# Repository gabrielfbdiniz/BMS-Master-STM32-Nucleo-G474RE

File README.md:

# BMS Master — STM32 Nucleo G474RE (Formula ITA)
### ECU Central de Gerenciamento do Acumulador de Tração (20s18p)

Repositório oficial e unificado (**Monorepo**) de **Hardware**, **Firmware** e **Documentação de Engenharia** do BMS Master desenvolvido para o protótipo Formula SAE Electric da equipe **Formula ITA** (Temporada 2025-2026).

---

## Renderização 3D da Carrier Board

A placa **BMS Master Carrier Shield** é uma PCB de 4 camadas projetada para acoplar o núcleo de processamento **ST NUCLEO-G474RE** via conectores Morpho, integrando circuitos de proteção automotiva, barreira galvânica e interface com o circuito de segurança (SDC).

<div align="center">
  
  <p><em>Vista Isométrica Superior — Destaque para o transformador de pulso Pulse HMU2103NL (Iso-SPI), relé automotivo TE do SDC, regulador buck automotivo e conectores Molex Micro-Fit.</em></p>
</div>

<br>

### Galeria de Vistas 3D (KiCad 10 Raytracing)

| Perspectiva Superior (Iso Top) | Perspectiva Inferior (Iso Bottom) |
| :---: | :---: |
|  |  |
| **Vista Ortográfica Superior (Top View)** | **Vista Ortográfica Inferior (Bottom View)** |
|  |  |

---

## Destaques do Projeto de Hardware

* **Topologia do Acumulador:** 20 blocos em série, cada bloco com 18 células em paralelo (**20s18p = 360 células** formato 21700).
* **Processamento Central:** ST NUCLEO-G474RE (MCU ARM Cortex-M4F com FPU a 170 MHz, 512 kB Flash, 128 kB SRAM).
* **Barreira de Isolação Iso-SPI (FSAE EV4.8):** Transceptor ST `L99BM1TR` acoplado a transformador de isolação `Pulse HMU2103NL` ($\ge 2500\text{ V}_{RMS}$, creepage $\ge 4{,}0\text{ mm}$).
* **Interface SDC Hardware Latch:** Circuito biestável puramente em hardware com reset supervisionado, garantindo abertura mandatória da linha de shutdown em qualquer falha crítica.
* **Alimentação e Proteção GLV:** Buck automotivo `TI LMR36510` (12V $\to$ 5V) com supressor TVS SMAJ, diodo Schottky contra inversão de polaridade e filtragem para normas ISO 7637-2.
* **Comunicação Veicular:** CAN-FD isolada galvanicamente via transceptor `TI ISO1042` (suporte a até 5 Mbps).

---

## Estrutura do Repositório (Monorepo)

```text
BMS Master - STM - V0/
├── .gitignore                         # Regras de exclusão Git (KiCad, builds, temporários)
├── README.md                          # Visão geral, especificações e documentação rápida
├── docs/                              # Engenharia de sistemas, especificações e manuais
│   ├── schematics/                    # Esquemáticos oficiais em PDF vetorial
│   │   └── BMS_Master_Schematic.pdf   # Esquemático hierárquico vetorial completo (KiCad 10)
│   ├── PLANO_MESTRE_BMS_MASTER_CONSOLIDADO.md  # Especificação técnica completa do sistema
│   ├── MANUAL_OPERACIONAL_E_MONTAGEM_BMS.md    # Procedimentos de montagem, testes e comissionamento
│   ├── PLANO_DETECCAO_FUSIVEL_METODO_1.md      # Formulação matemática do algoritmo RLS e Z-score
│   ├── GUIA_ENSAIO_CARACTERIZACAO_CELULAS_21700.md # Manual de bancada HPPC (FreedomCAR)
│   └── ARQUITETURA_E_PLANEJAMENTO_BMS_MASTER.md    # Arquitetura conceitual e interfaces
│
├── hardware/                          # Projeto Eletrônico no KiCad 10
│   └── carrier_shield/                # Carrier Board de 4 camadas para NUCLEO-G474RE
│       ├── bms_carrier_shield.kicad_pro  # Projeto mestre KiCad
│       ├── bms_carrier_shield.kicad_sch  # Esquemático mestre
│       ├── bms_carrier_shield.kicad_pcb  # Layout de 4 camadas (Top/GND/PWR/Bot)
│       ├── 01_power_supply.kicad_sch     # Folha: Regulador GLV 12V -> 5V
│       ├── 02_isospi_barrier.kicad_sch   # Folha: Barreira Iso-SPI L99BM1TR + HMU2103NL
│       ├── 03_sdc_latch.kicad_sch        # Folha: Circuito Latch biestável do SDC
│       ├── 05_canfd_interface.kicad_sch  # Folha: Interface CAN-FD isolada ISO1042
│       ├── 06_nucleo_headers.kicad_sch   # Folha: Conectores Morpho NUCLEO-G474RE
│       ├── fp-lib-table, sym-lib-table   # Mapeamento local de bibliotecas
│       ├── libraries/                    # Modelos 3D (.stp/.wrl), símbolos e footprints
│       └── fabrication/                  # Pacote de manufatura e montagem SMT
│           ├── FABRICATION_NOTES.md      # Especificações para fabricação da placa
│           ├── gerbers/                  # Arquivos Gerber RS-274X e Drill Excellon (ZIP)
│           ├── bom/                      # Listas de materiais (CSV, TSV, Mouser, Interactive BOM)
│           └── cpl/                      # Arquivo de posicionamento Pick & Place (pos.csv)
│
├── renders/                           # Renderizações fotorrealistas em alta resolução da PCB (KiCad 10)
│   ├── master_render_iso_top.png
│   ├── master_render_iso_bottom.png
│   ├── master_render_top.png
│   └── master_render_bottom.png
│
├── firmware/                          # Código em C99 Puro (ARM Cortex-M4F & Simulação SIL)
│   ├── core/                          # Algoritmos puros desacoplados de hardware
│   │   ├── bms_types.h                # Definições da topologia 20s18p, limites e telemetria
│   │   ├── alg_fuse_detect.c/.h       # RLS incremental, Z-score e Pre-Flight Check de fusíveis
│   │   ├── alg_soc.c/.h               # Coulomb counting, tabela OCV e limites CCL/DCL dinâmicos
│   │   └── fsm_master.c/.h            # Máquina de estados finitos (FSAE EV4.8 / EV8)
│   ├── mock/                          # Motor de sensoriamento sintético de alta fidelidade
│   ├── tests_sil/                     # Testes de Software-in-the-Loop (SIL) no Host (PC)
│   └── tools/                         # Scripts de simulação e plotagem em Python
│
├── can/                               # Matriz de comunicação veicular CAN-FD
│   ├── README.md                      # Documentação das mensagens CAN e taxas de atualização
│   └── bms_can_matrix.dbc             # Arquivo DBC padronizado
│
└── simulation/                        # Simulação de circuitos analógicos (Proteus VSM)
    └── proteus_sdc_precharge/         # Circuito biestável SDC e transitório RC de pré-carga
```

---

## Software-in-the-Loop (SIL) & Validação de Algoritmos

O firmware foi projetado segundo a arquitetura de **Core Desacoplado**, permitindo que 100% dos algoritmos de segurança, estimativa de estado e detecção de anomalias sejam validados no computador host antes do deployment no microcontrolador:

1. **Detecção de Fusível Rompido via RLS:** Estima recursivamente a resistência interna $\hat{R}_i$ de cada bloco em tempo real durante a descarga ($0{,}833\text{ m}\Omega \to 0{,}882\text{ m}\Omega$, delta de $+49\ \mu\Omega$).
2. **Estimador de SOC Híbrido:** Integração Coulomb Counting compensada por OCV relaxado com limites dinâmicos de corrente de carga (CCL) e descarga (DCL).
3. **FSM Conforme FSAE:** Transições estritas entre `BOOT`, `PRECHARGE`, `DRIVE`, `CHARGING`, `FAULT` e travamento por Latch em caso de violação de envelope seguro.

<div align="center">
  
  <p><em>Curvas de resposta dinâmica: Corrente do perfil de corrida, tensões das células, evolução da resistência estimada por RLS com injeção de falha aos 20s e transições de estado da FSM.</em></p>
</div>

### Executando a Simulação SIL Localmente

No terminal, dentro do diretório `firmware/`:

```powershell
# 1. Compilar e rodar a simulação SIL nativa em C (60 segundos virtuais a 100 Hz)
clang -O2 -Wall -Icore -Imock tests_sil/main_sil_runner.c core/alg_fuse_detect.c core/alg_soc.c core/fsm_master.c mock/bms_mock_battery.c mock/drive_cycle.c -o tests_sil/sil_runner.exe -lm
.\tests_sil\sil_runner.exe

# 2. Gerar/atualizar os gráficos de telemetria
python tools/plot_telemetry.py
```

---

## Como Abrir o Projeto Eletrônico no KiCad 10

1. Abra o **KiCad 10**.
2. Selecione **Abrir Projeto** e aponte para:  
   `hardware/carrier_shield/bms_carrier_shield.kicad_pro`.
3. Para visualizar a placa em 3D:
   - Abra o editor de PCB (`bms_carrier_shield.kicad_pcb`).
   - Pressione <kbd>Alt</kbd> + <kbd>3</kbd> para abrir o **Visualizador 3D**.
   - As bibliotecas de modelos (`libraries/3dmodels/`) já estão configuradas relativamente no projeto.
4. Para consultar o esquemático em PDF sem abrir o KiCad:
   - Abra diretamente: [`docs/schematics/BMS_Master_Schematic.pdf`](docs/schematics/BMS_Master_Schematic.pdf).

---

## Documentação Técnica de Referência

Consulte a pasta [`docs/`](docs/) para aprofundamento técnico:
* [**Esquemático Oficial (PDF)**](docs/schematics/BMS_Master_Schematic.pdf) — Desenho esquemático elétrico completo vetorial.
* [**Plano Mestre Consolidado**](docs/PLANO_MESTRE_BMS_MASTER_CONSOLIDADO.md) — Documento mestre de especificação técnica e funcional.
* [**Manual Operacional e de Montagem**](docs/MANUAL_OPERACIONAL_E_MONTAGEM_BMS.md) — Roteiro detalhado de fabricação, montagem de chicotes e testes de bancada.
* [**Plano de Detecção de Fusível Rompido**](docs/PLANO_DETECCAO_FUSIVEL_METODO_1.md) — Formulação matemática do RLS incremental e teste Z-score.
* [**Guia de Caracterização de Células 21700**](docs/GUIA_ENSAIO_CARACTERIZACAO_CELULAS_21700.md) — Protocolo de ensaio experimental HPPC em bancada.

---

<div align="center">
  <sub>Formula ITA — Equipe de Formula SAE Elétrico do Instituto Tecnológico de Aeronáutica (ITA).</sub>
</div>

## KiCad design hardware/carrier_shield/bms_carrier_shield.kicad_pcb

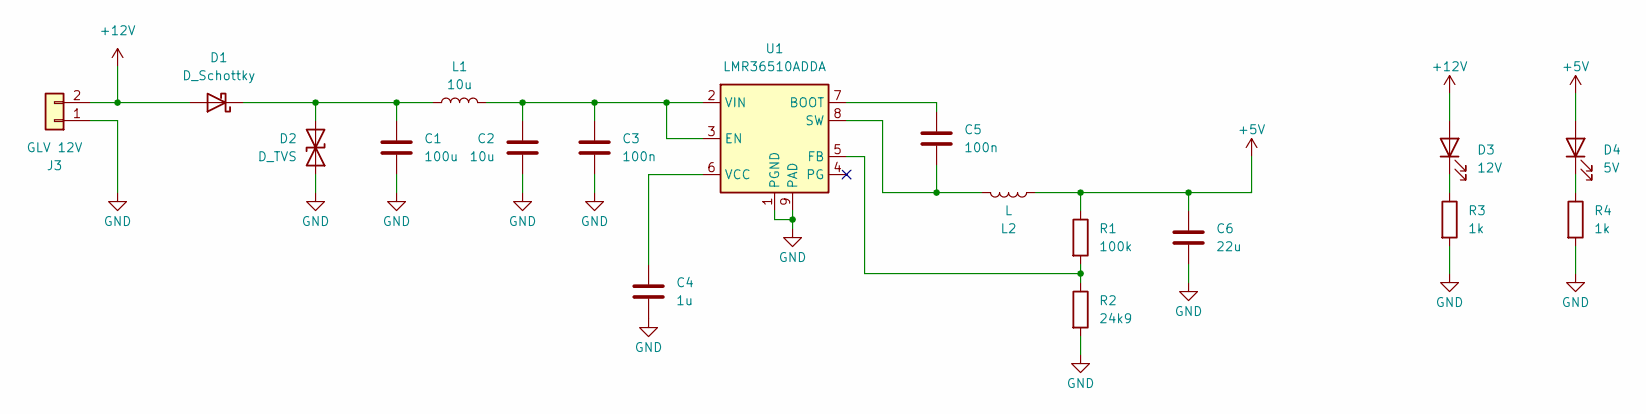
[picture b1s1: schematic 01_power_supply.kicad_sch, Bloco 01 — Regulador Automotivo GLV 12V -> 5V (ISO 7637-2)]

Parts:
C1: 100u; CP_Elec_8x10
C2: 10u; C_0805_2012Metric_Pad1.18x1.45mm_HandSolder
C3, C5: 100n; C_0603_1608Metric_Pad1.08x0.95mm_HandSolder
C4: 1u; C_0603_1608Metric_Pad1.08x0.95mm_HandSolder
C6: 22u; C_0805_2012Metric_Pad1.18x1.45mm_HandSolder
D1: D_Schottky; D_SMA
D2: D_TVS; D_SMA
D3: 12V; LED_0805_2012Metric_Pad1.15x1.40mm_HandSolder
D4: 5V; LED_0805_2012Metric_Pad1.15x1.40mm_HandSolder
J3: GLV 12V; AMASS_XT30U-F_1x02_P5.0mm_Vertical
L1: 10u; L_Bourns_SRR1260
L2: L; L_Bourns_SRR1260
R1: 100k; R_0603_1608Metric_Pad0.98x0.95mm_HandSolder
R2: 24k9; R_0603_1608Metric_Pad0.98x0.95mm_HandSolder
R3, R4: 1k; R_0603_1608Metric_Pad0.98x0.95mm_HandSolder
U1: LMR36510ADDA; Texas_HTSOP-8-1EP_3.9x4.9mm_P1.27mm_EP2.95x4.9mm_Mask2.4x3.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

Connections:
+5V: C6.1, D4.2 (A), L2.2, R1.1; also elsewhere on the board
+12V: D1.2 (A), D3.2 (A), J3.2; also elsewhere on the board
GND: C1.2, C2.2, C3.2, C4.2, C6.2, D2.1 (A1), J3.1, R2.2, R3.2, R4.2, U1.1 (PGND), U1.9 (PAD); also elsewhere on the board
unnamed: C1.1, D1.1 (K), D2.2 (A2), L1.1
unnamed: D3.1 (K), R3.1
unnamed: D4.1 (K), R4.1
unnamed: C5.1, U1.7 (BOOT)
unnamed: C2.1, C3.1, L1.2, U1.2 (VIN), U1.3 (EN)
unnamed: R1.2, R2.1, U1.5 (FB)
unnamed: C5.2, L2.1, U1.8 (SW)
unnamed: C4.1, U1.6 (VCC)

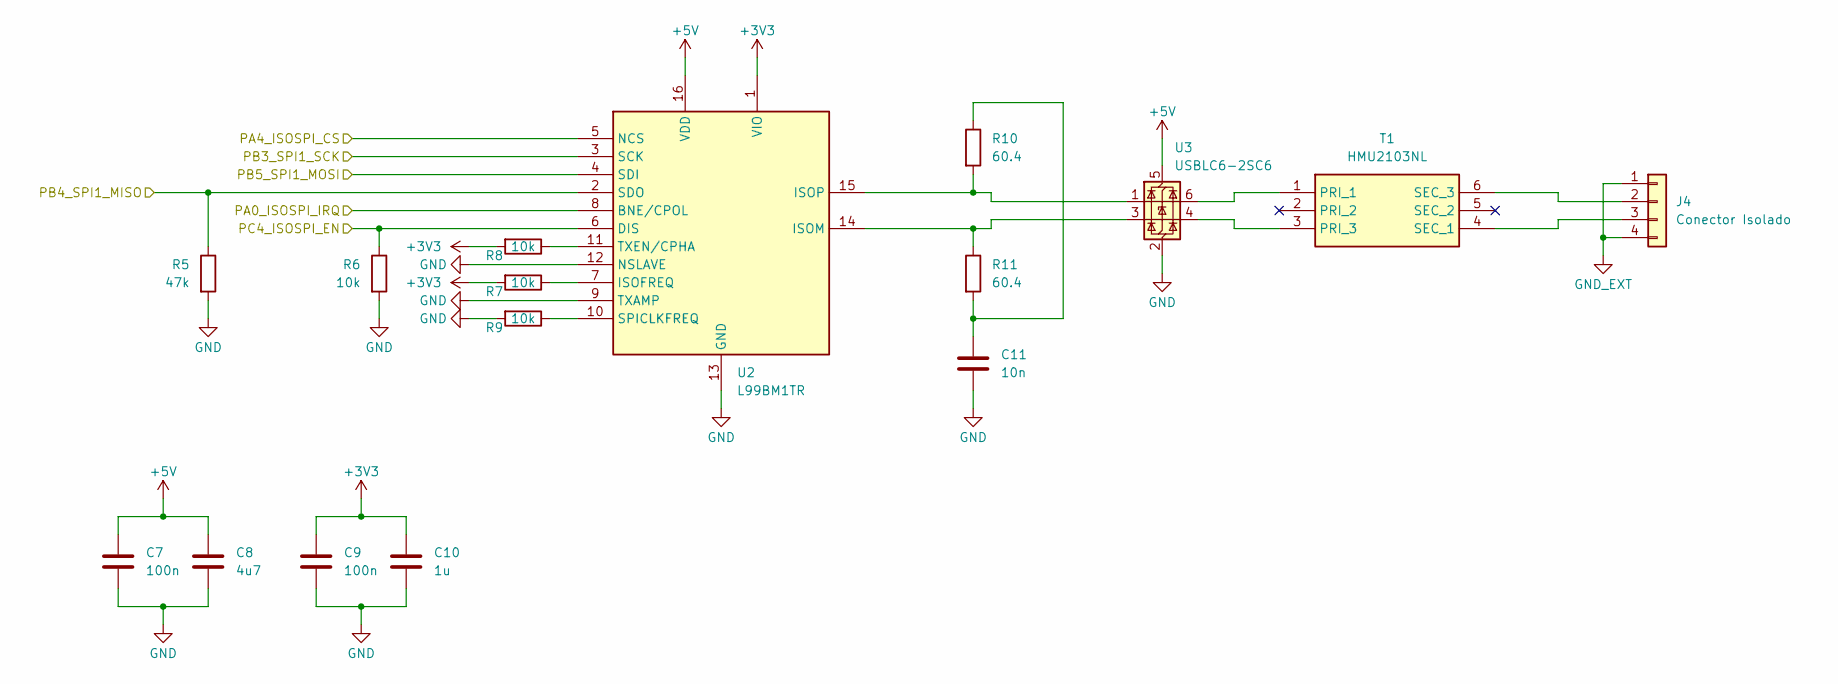
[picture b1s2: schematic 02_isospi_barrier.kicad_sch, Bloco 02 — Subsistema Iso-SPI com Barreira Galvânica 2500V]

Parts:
C7, C9: 100n; C_0603_1608Metric_Pad1.08x0.95mm_HandSolder
C8: 4u7; C_0805_2012Metric_Pad1.18x1.45mm_HandSolder
C10: 1u; C_0603_1608Metric_Pad1.08x0.95mm_HandSolder
C11: 10n; C_0603_1608Metric_Pad1.08x0.95mm_HandSolder
J4: Conector Isolado; Molex_Micro-Fit_3.0_43650-0400_1x04_P3.00mm_Horizontal
R5: 47k; R_0603_1608Metric_Pad0.98x0.95mm_HandSolder
R6, R7, R8, R9: 10k; R_0603_1608Metric_Pad0.98x0.95mm_HandSolder
R10, R11: 60.4; R_0603_1608Metric_Pad0.98x0.95mm_HandSolder
T1: HMU2103NL; Mouser Part Number 673-HMU2103NL
U2: L99BM1TR; SOIC-16_3.9x9.9mm_P1.27mm; Manufacturer_Part_Number L99BM1TR
U3: USBLC6-2SC6; SOT-23-6

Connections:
+3V3: C9.1, C10.1, R7.2, R8.2, U2.1 (VIO); also elsewhere on the board
+5V: C7.1, C8.1, U2.16 (VDD), U3.5 (VBUS); also elsewhere on the board
/05_Nucleo_G474RE_Morpho_Headers/PA0_ISOSPI_IRQ: U2.8 (BNE/CPOL); also elsewhere on the board
/05_Nucleo_G474RE_Morpho_Headers/PA4_ISOSPI_CS: U2.5 (NCS); also elsewhere on the board
/05_Nucleo_G474RE_Morpho_Headers/PB3_SPI1_SCK: U2.3 (SCK); also elsewhere on the board
/05_Nucleo_G474RE_Morpho_Headers/PB4_SPI1_MISO: R5.1, U2.2 (SDO); also elsewhere on the board
/05_Nucleo_G474RE_Morpho_Headers/PB5_SPI1_MOSI: U2.4 (SDI); also elsewhere on the board
/05_Nucleo_G474RE_Morpho_Headers/PC4_ISOSPI_EN: R6.1, U2.6 (DIS); also elsewhere on the board
GND: C7.2, C8.2, C9.2, C10.2, C11.2, R5.2, R6.2, R9.2, U2.9 (TXAMP), U2.12 (NSLAVE), U2.13 (GND), U3.2 (GND); also elsewhere on the board
GND_EXT: J4.1, J4.4
unnamed: C11.1, R10.1, R11.2
unnamed: J4.2, T1.6 (SEC_3)
unnamed: J4.3, T1.4 (SEC_1)
unnamed: T1.1 (PRI_1), U3.6 (I/O1)
unnamed: T1.3 (PRI_3), U3.4 (I/O2)
unnamed: R7.1, U2.7 (ISOFREQ)
unnamed: R11.1, U2.14 (ISOM), U3.3 (I/O2)
unnamed: R10.2, U2.15 (ISOP), U3.1 (I/O1)
unnamed: R9.1, U2.10 (SPICLKFREQ)
unnamed: R8.1, U2.11 (TXEN/CPHA)

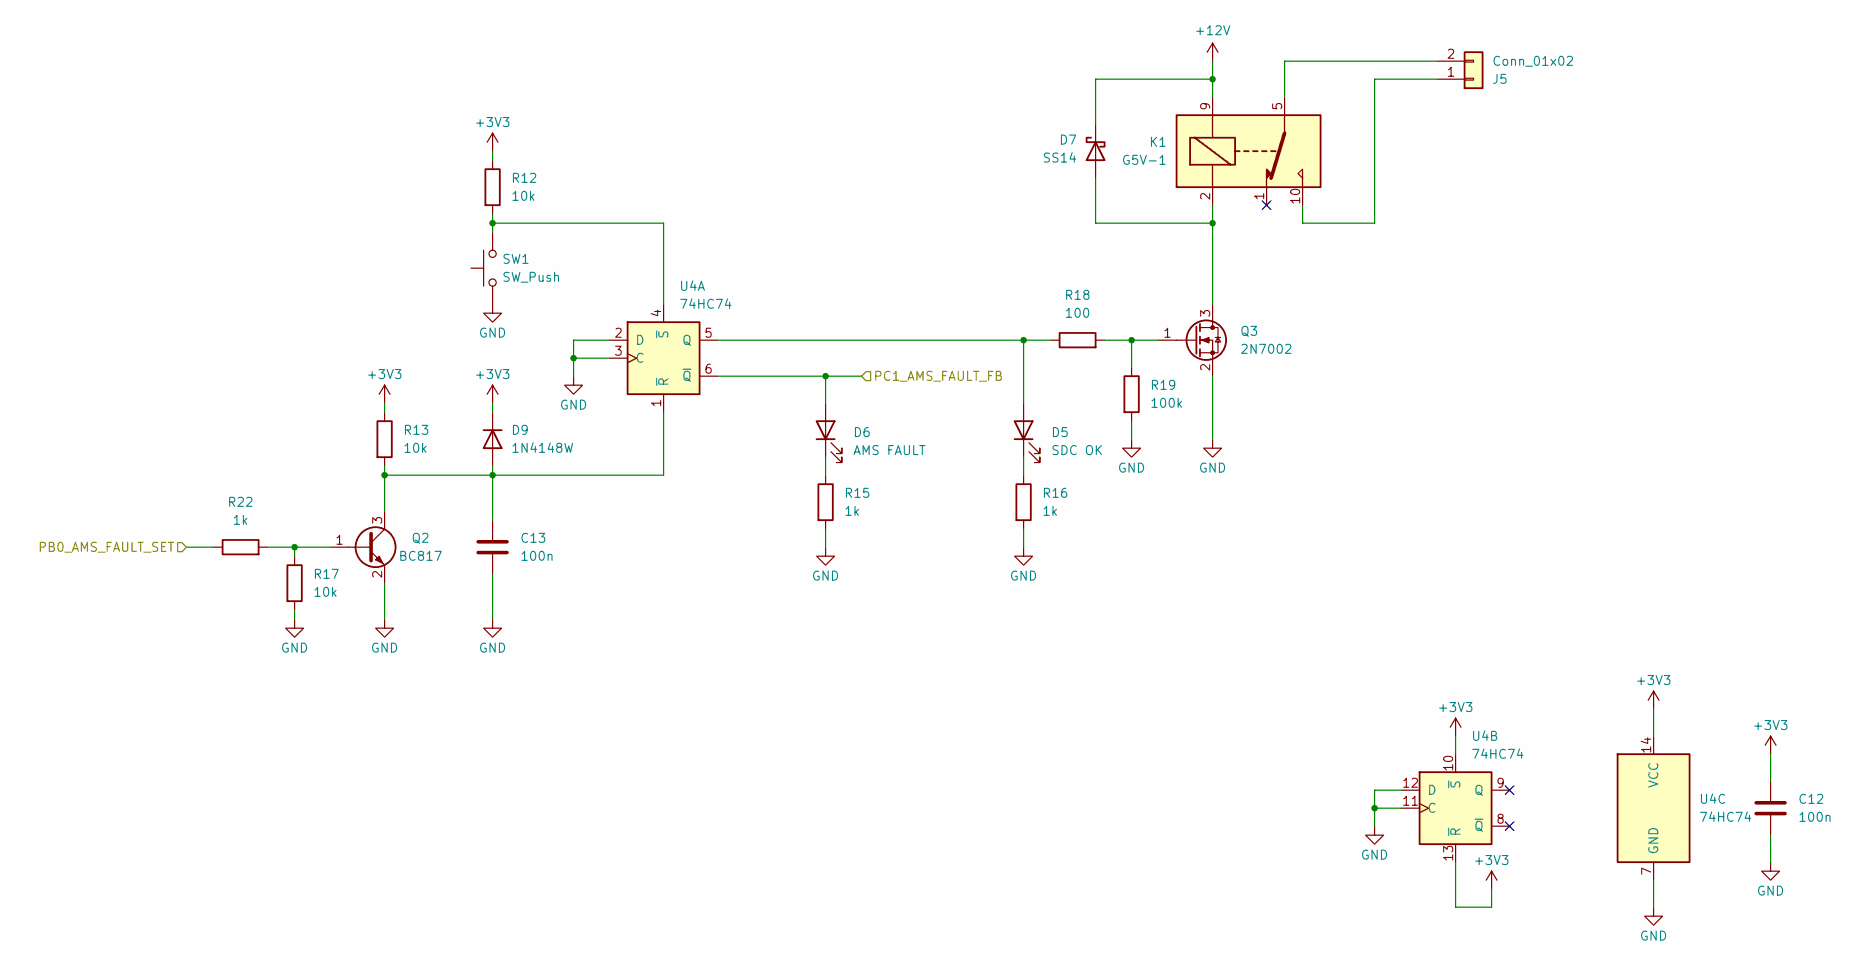
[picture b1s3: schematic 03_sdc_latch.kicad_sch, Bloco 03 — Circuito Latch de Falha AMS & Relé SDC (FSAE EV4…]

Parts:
C12: 100n; C_0603_1608Metric_Pad1.08x0.95mm_HandSolder
C13: 100n
D5: SDC OK; LED_0805_2012Metric_Pad1.15x1.40mm_HandSolder
D6: AMS FAULT; LED_0805_2012Metric_Pad1.15x1.40mm_HandSolder
D7: SS14; D_SMA
D9: 1N4148W; D_SOD-123
J5: Conn_01x02; Molex_Micro-Fit_3.0_43650-0200_1x02_P3.00mm_Horizontal
K1: G5V-1; Relay_SPDT_Omron_G5V-1
Q2: BC817; SOT-23
Q3: 2N7002; SOT-23
R12, R13, R17: 10k; R_0603_1608Metric_Pad0.98x0.95mm_HandSolder
R15, R16, R22: 1k; R_0603_1608Metric_Pad0.98x0.95mm_HandSolder
R18: 100; R_0603_1608Metric_Pad0.98x0.95mm_HandSolder
R19: 100k; R_0603_1608Metric_Pad0.98x0.95mm_HandSolder
SW1: SW_Push; SW_PUSH_6mm_H5mm
U4: 74HC74; SOIC-14_3.9x8.7mm_P1.27mm

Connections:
+3V3: C12.1, D9.1 (K), R12.1, R13.1, U4.10 (~S), U4.13 (~R), U4.14 (VCC); also elsewhere on the board
+12V: D7.1 (K), K1.9; also elsewhere on the board
/05_Nucleo_G474RE_Morpho_Headers/PB0_AMS_FAULT_SET: R22.1; also elsewhere on the board
/05_Nucleo_G474RE_Morpho_Headers/PC1_AMS_FAULT_FB: D6.2 (A), U4.6 (~Q); also elsewhere on the board
GND: C12.2, C13.2, Q2.2 (E), Q3.2 (S), R15.2, R16.2, R17.2, R19.2, SW1.1, U4.2 (D), U4.3 (C), U4.7 (GND), U4.11 (C), U4.12 (D); also elsewhere on the board
unnamed: D5.2 (A), R18.1, U4.5 (Q)
unnamed: D5.1 (K), R16.1
unnamed: D6.1 (K), R15.1
unnamed: D7.2 (A), K1.2, Q3.3 (D)
unnamed: C13.1, D9.2 (A), Q2.3 (C), R13.2, U4.1 (~R)
unnamed: J5.1, K1.10
unnamed: J5.2, K1.5, K1.6
unnamed: Q2.1 (B), R17.1, R22.2
unnamed: Q3.1 (G), R18.2, R19.1
unnamed: R12.2, SW1.2, U4.4 (~S)

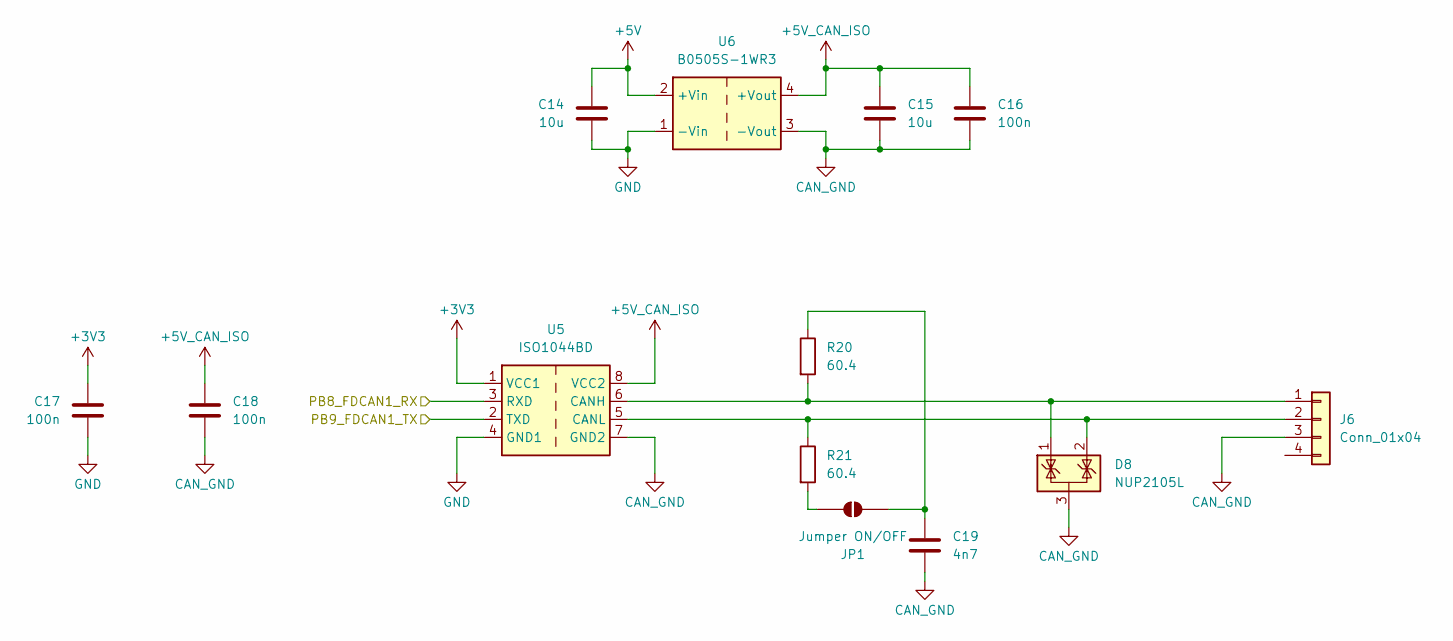
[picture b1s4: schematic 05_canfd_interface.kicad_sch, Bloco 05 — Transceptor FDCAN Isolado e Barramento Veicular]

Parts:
C14, C15: 10u; C_0805_2012Metric_Pad1.18x1.45mm_HandSolder
C16, C17, C18: 100n; C_0603_1608Metric_Pad1.08x0.95mm_HandSolder
C19: 4n7; C_0603_1608Metric_Pad1.08x0.95mm_HandSolder
D8: NUP2105L; SOT-23
J6: Conn_01x04; Molex_Micro-Fit_3.0_43650-0400_1x04_P3.00mm_Horizontal
JP1: Jumper ON/OFF; SolderJumper-2_P1.3mm_Open_Pad1.0x1.5mm
R20, R21: 60.4; R_0603_1608Metric_Pad0.98x0.95mm_HandSolder
U5: ISO1044BD; SOIC-8_3.9x4.9mm_P1.27mm
U6: B0505S-1WR3; Converter_DCDC_Murata_MEE1SxxxxSC_THT

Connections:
+3V3: C17.1, U5.1 (VCC1); also elsewhere on the board
+5V: C14.1, U6.2 (+Vin); also elsewhere on the board
+5V_CAN_ISO: C15.1, C16.1, C18.1, U5.8 (VCC2), U6.4 (+Vout)
/05_Nucleo_G474RE_Morpho_Headers/PB8_FDCAN1_RX: U5.2 (TXD); also elsewhere on the board
/05_Nucleo_G474RE_Morpho_Headers/PB9_FDCAN1_TX: U5.3 (RXD); also elsewhere on the board
CAN_GND: C15.2, C16.2, C18.2, C19.2, D8.3 (A), J6.3, U5.7 (GND2), U6.3 (-Vout)
GND: C14.2, C17.2, U5.4 (GND1), U6.1 (-Vin); also elsewhere on the board
unnamed: D8.1 (K), J6.1, R20.2, U5.6 (CANH)
unnamed: D8.2 (K), J6.2, R21.1, U5.5 (CANL)
unnamed: JP1.1 (A), R21.2
unnamed: C19.1, JP1.2 (B), R20.1

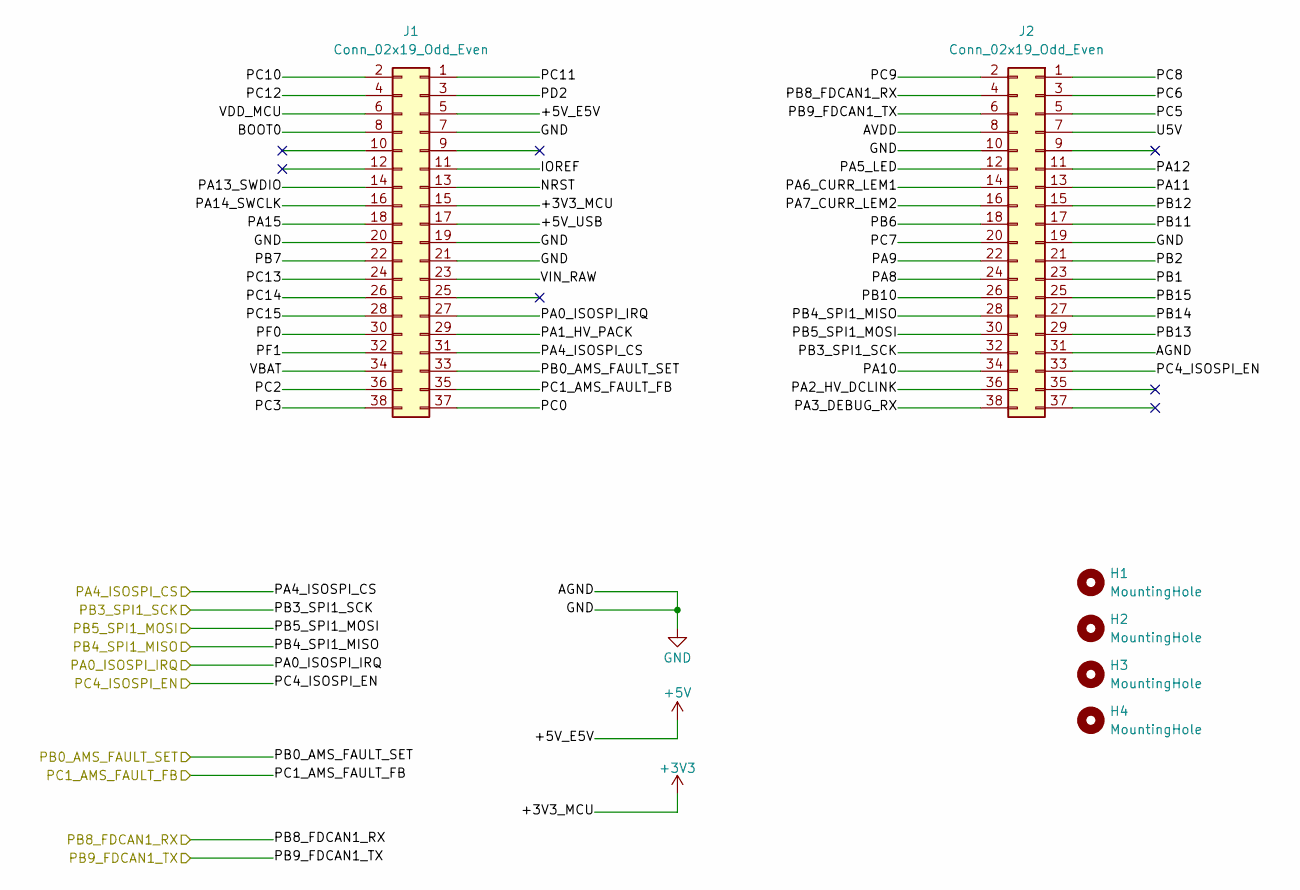
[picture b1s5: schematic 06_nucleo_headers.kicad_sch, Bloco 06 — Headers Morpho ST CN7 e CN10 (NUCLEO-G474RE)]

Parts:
H1, H2, H3, H4: MountingHole; MountingHole_3.2mm_M3
J1, J2: Conn_02x19_Odd_Even; PinSocket_2x19_P2.54mm_Vertical

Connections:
+3V3: J1.15; also elsewhere on the board
+5V: J1.5; also elsewhere on the board
/05_Nucleo_G474RE_Morpho_Headers/+5V_USB: J1.17
/05_Nucleo_G474RE_Morpho_Headers/AVDD: J2.8
/05_Nucleo_G474RE_Morpho_Headers/BOOT0: J1.8
/05_Nucleo_G474RE_Morpho_Headers/IOREF: J1.11
/05_Nucleo_G474RE_Morpho_Headers/NRST: J1.13
/05_Nucleo_G474RE_Morpho_Headers/PA0_ISOSPI_IRQ: J1.27; also elsewhere on the board
/05_Nucleo_G474RE_Morpho_Headers/PA1_HV_PACK: J1.29
/05_Nucleo_G474RE_Morpho_Headers/PA2_HV_DCLINK: J2.36
/05_Nucleo_G474RE_Morpho_Headers/PA3_DEBUG_RX: J2.38
/05_Nucleo_G474RE_Morpho_Headers/PA4_ISOSPI_CS: J1.31; also elsewhere on the board
/05_Nucleo_G474RE_Morpho_Headers/PA5_LED: J2.12
/05_Nucleo_G474RE_Morpho_Headers/PA6_CURR_LEM1: J2.14
/05_Nucleo_G474RE_Morpho_Headers/PA7_CURR_LEM2: J2.16
/05_Nucleo_G474RE_Morpho_Headers/PA8: J2.24
/05_Nucleo_G474RE_Morpho_Headers/PA9: J2.22
/05_Nucleo_G474RE_Morpho_Headers/PA10: J2.34
/05_Nucleo_G474RE_Morpho_Headers/PA11: J2.13
/05_Nucleo_G474RE_Morpho_Headers/PA12: J2.11
/05_Nucleo_G474RE_Morpho_Headers/PA13_SWDIO: J1.14
/05_Nucleo_G474RE_Morpho_Headers/PA14_SWCLK: J1.16
/05_Nucleo_G474RE_Morpho_Headers/PA15: J1.18
/05_Nucleo_G474RE_Morpho_Headers/PB0_AMS_FAULT_SET: J1.33; also elsewhere on the board
/05_Nucleo_G474RE_Morpho_Headers/PB1: J2.23
/05_Nucleo_G474RE_Morpho_Headers/PB2: J2.21
/05_Nucleo_G474RE_Morpho_Headers/PB3_SPI1_SCK: J2.32; also elsewhere on the board
/05_Nucleo_G474RE_Morpho_Headers/PB4_SPI1_MISO: J2.28; also elsewhere on the board
/05_Nucleo_G474RE_Morpho_Headers/PB5_SPI1_MOSI: J2.30; also elsewhere on the board
/05_Nucleo_G474RE_Morpho_Headers/PB6: J2.18
/05_Nucleo_G474RE_Morpho_Headers/PB7: J1.22
/05_Nucleo_G474RE_Morpho_Headers/PB8_FDCAN1_RX: J2.4; also elsewhere on the board
/05_Nucleo_G474RE_Morpho_Headers/PB9_FDCAN1_TX: J2.6; also elsewhere on the board
/05_Nucleo_G474RE_Morpho_Headers/PB10: J2.26
/05_Nucleo_G474RE_Morpho_Headers/PB11: J2.17
/05_Nucleo_G474RE_Morpho_Headers/PB12: J2.15
/05_Nucleo_G474RE_Morpho_Headers/PB13: J2.29
/05_Nucleo_G474RE_Morpho_Headers/PB14: J2.27
/05_Nucleo_G474RE_Morpho_Headers/PB15: J2.25
/05_Nucleo_G474RE_Morpho_Headers/PC0: J1.37
/05_Nucleo_G474RE_Morpho_Headers/PC1_AMS_FAULT_FB: J1.35; also elsewhere on the board
/05_Nucleo_G474RE_Morpho_Headers/PC2: J1.36
/05_Nucleo_G474RE_Morpho_Headers/PC3: J1.38
/05_Nucleo_G474RE_Morpho_Headers/PC4_ISOSPI_EN: J2.33; also elsewhere on the board
/05_Nucleo_G474RE_Morpho_Headers/PC5: J2.5
/05_Nucleo_G474RE_Morpho_Headers/PC6: J2.3
/05_Nucleo_G474RE_Morpho_Headers/PC7: J2.20
/05_Nucleo_G474RE_Morpho_Headers/PC8: J2.1
/05_Nucleo_G474RE_Morpho_Headers/PC9: J2.2
/05_Nucleo_G474RE_Morpho_Headers/PC10: J1.2
/05_Nucleo_G474RE_Morpho_Headers/PC11: J1.1
/05_Nucleo_G474RE_Morpho_Headers/PC12: J1.4
/05_Nucleo_G474RE_Morpho_Headers/PC13: J1.24
/05_Nucleo_G474RE_Morpho_Headers/PC14: J1.26
/05_Nucleo_G474RE_Morpho_Headers/PC15: J1.28
/05_Nucleo_G474RE_Morpho_Headers/PD2: J1.3
/05_Nucleo_G474RE_Morpho_Headers/PF0: J1.30
/05_Nucleo_G474RE_Morpho_Headers/PF1: J1.32
/05_Nucleo_G474RE_Morpho_Headers/U5V: J2.7
/05_Nucleo_G474RE_Morpho_Headers/VBAT: J1.34
/05_Nucleo_G474RE_Morpho_Headers/VDD_MCU: J1.6
/05_Nucleo_G474RE_Morpho_Headers/VIN_RAW: J1.23
GND: J1.7, J1.19, J1.20, J1.21, J2.10, J2.19, J2.31; also elsewhere on the board

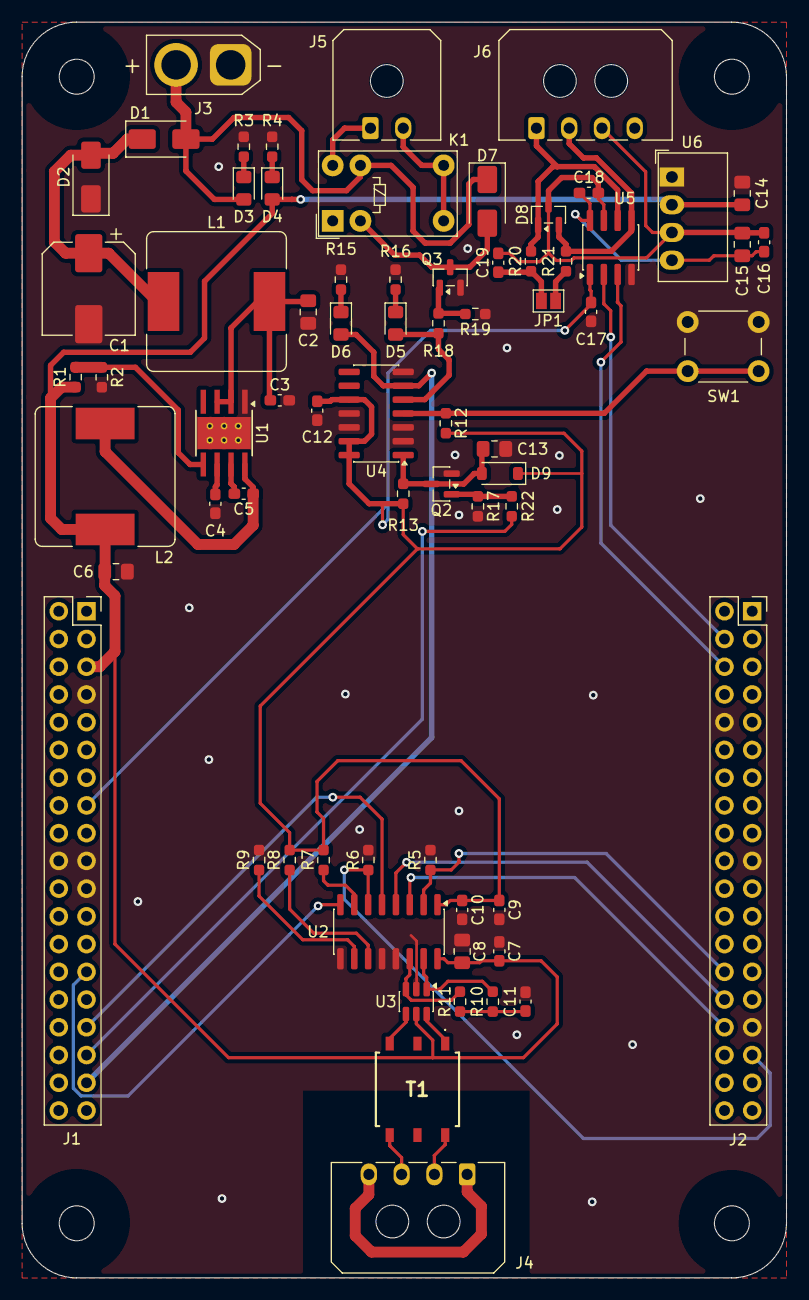
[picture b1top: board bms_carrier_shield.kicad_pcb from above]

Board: 4 copper layers, 70.0 x 115.0 mm, 73 parts (0 on the bottom side), 49 nets.

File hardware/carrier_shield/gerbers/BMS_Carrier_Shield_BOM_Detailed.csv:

Item,Designator,Quantity,Value,Package,Description,Manufacturer,MPN,LCSC_Mouser
1,U1,1,LMR36510ADDA,HTSOP-8-EP (3.9x4.9mm),Automotive Synchronous Step-Down Voltage Regulator 65V 1A,Texas Instruments,LMR36510ADDAR,Mouser: 595-LMR36510ADDAR / LCSC: C2682705
2,U2,1,L99BM1TR,SOIC-16 (3.9x9.9mm),Automotive Isolated SPI Physical Layer Transceiver,STMicroelectronics,L99BM1TR,Mouser: 511-L99BM1TR
3,U3,1,USBLC6-2SC6,SOT-23-6,Very Low Capacitance ESD Protection Diode Array,STMicroelectronics,USBLC6-2SC6,Mouser: 511-USBLC6-2SC6 / LCSC: C7519
4,U4,1,74HC74,SOIC-14 (3.9x8.7mm),Dual D-Type Positive-Edge-Triggered Flip-Flop with Clear and Preset,Texas Instruments,SN74HC74DR,Mouser: 595-SN74HC74DR / LCSC: C5595
5,U5,1,ISO1044BD,SOIC-8 (3.9x4.9mm),Galvanically Isolated CAN-FD Transceiver with 5000-Vrms Isolation,Texas Instruments,ISO1044BDR,Mouser: 595-ISO1044BDR / LCSC: C711585
6,U6,1,B0505S-1WR3,SIP-4 (11.5x6.0mm THT),Isolated DC-DC Converter 5V to 5V 1W 3kVDC Isolation,Mornsun,B0505S-1WR3,LCSC: C148866 / Mouser: 805-B0505S-1WR3
7,T1,1,HMU2103NL,SMD-16 (16.2x11.8mm),Dual-Channel Automotive Iso-SPI Pulse Transformer 2500Vrms 4.0mm Creepage,Pulse Electronics,HMU2103NL,Mouser: 673-HMU2103NL
8,K1,1,G5V-1-DC5,THT DIP (12.5x7.5mm),Ultra-miniature SPDT Low Signal Relay 5VDC Coil 1A Contact,Omron Electronics,G5V-1-DC5,Mouser: 653-G5V-1-DC5 / LCSC: C38198
9,Q2,1,BC817-40,SOT-23,NPN General Purpose BJT 45V 500mA,Nexperia,"BC817-40,215",Mouser: 771-BC817-40215 / LCSC: C109033
10,Q3,1,2N7002,SOT-23,N-Channel Enhancement Mode MOSFET 60V 115mA,Diodes Incorporated,2N7002-7-F,Mouser: 621-2N7002-F / LCSC: C8502
11,D1,1,B340A / SS34,SMA (DO-214AC),Schottky Barrier Rectifier Diode 40V 3A (Reverse Polarity Protection),Diodes Incorporated,B340A-13-F,Mouser: 621-B340A-F / LCSC: C15950
12,D2,1,SMAJ15CA,SMA (DO-214AC),Bidirectional Transient Voltage Suppressor (TVS) Diode 15V Vrwm 400W,Littelfuse,SMAJ15CA,Mouser: 576-SMAJ15CA / LCSC: C81747
13,D7,1,SS14,SMA (DO-214AC),Schottky Rectifier Diode 40V 1A (Flyback suppression),Diodes Incorporated,B140-13-F,Mouser: 621-B140-F / LCSC: C1577
14,D8,1,NUP2105L,SOT-23,Dual Bidirectional Automotive CAN Bus TVS Protection Diode 24V,onsemi,NUP2105LT1G,Mouser: 863-NUP2105LT1G / LCSC: C14444
15,"D3, D4, D5",3,Green LED,0805 (2012 Metric),"SMD LED Green (12V GLV Power, 5V Logic Rail, SDC Status OK)",Lite-On,LTST-C170GKT,Mouser: 859-LTST-C170GKT / LCSC: C72043
16,D6,1,Red LED,0805 (2012 Metric),SMD LED Red (AMS Fault Indicator),Lite-On,LTST-C170CKT,Mouser: 859-LTST-C170CKT / LCSC: C72038
17,SW1,1,PTS645SL43,6.0x6.0mm THT H=5.0mm,Tactile Push Button SPST-NO (Manual SDC Reset),C&K / Littelfuse,PTS645SL43-2 LFS,Mouser: 611-PTS645SL43-2LFS / LCSC: C318884
18,"J1, J2",2,Morpho Female 2x19,2.54mm Pitch 2x19 Socket THT,Female Header Receptacle Strip 38-pin (NUCLEO-G474RE Morpho),Samtec / Amphenol,SSW-119-01-T-D,Mouser: 200-SSW11901TD
19,J3,1,XT30U-F / Micro-Fit 2P,XT30U-F / Molex 43650-0200,DC Power Input GLV 12V High-Reliability Connector,Amass / Molex,XT30U-F / 43650-0200,Mouser: 538-43650-0200
20,"J4, J6",2,Micro-Fit 3.0 4P RA,Molex 43650-0400 (3.0mm Pitch),Molex Micro-Fit 3.0 Single Row 4-Pin Right Angle Header (Iso-SPI & CAN),Molex,0436500400,Mouser: 538-43650-0400 / LCSC: C2687158
21,J5,1,Micro-Fit 3.0 2P RA,Molex 43650-0200 (3.0mm Pitch),Molex Micro-Fit 3.0 Single Row 2-Pin Right Angle Header (SDC Loop),Molex,0436500200,Mouser: 538-43650-0200 / LCSC: C2687156
22,"L1, L2",2,10uH 3.5A,Bourns SRR1260 (12.5x12.5x6.0mm),Shielded Power Inductor 10uH 3.5A+ (Buck output & Input Filter),Bourns,SRR1260-100M,Mouser: 652-SRR1260-100M / LCSC: C108047
23,C1,1,100uF 35V,Alum Elec SMD 8.0x10.0mm,Aluminum Electrolytic Capacitor Low-ESR 100uF 35V AEC-Q200,Panasonic,EEE-FK1V101P,Mouser: 667-EEE-FK1V101P / LCSC: C144131
24,"C2, C14, C15",3,10uF 25V,0805 (2012 Metric),Multilayer Ceramic Capacitor MLCC X7R 10uF 25V 10%,Murata,GRM21BZ71E106KE15L,Mouser: 81-GRM21BZ71E106KE5L / LCSC: C15850
25,C6,1,22uF 16V,0805 (2012 Metric),Multilayer Ceramic Capacitor MLCC X7R 22uF 16V 10%,Murata,GRM21BR71C226ME15L,Mouser: 81-GRM21BR71C226ME5L / LCSC: C96927
26,C8,1,4.7uF 25V,0805 (2012 Metric),Multilayer Ceramic Capacitor MLCC X7R 4.7uF 25V 10%,Murata,GRM21BR71E475KA73L,Mouser: 81-GRM21BR71E475KA3L / LCSC: C19666
27,"C4, C10",2,1uF 25V,0603 (1608 Metric),Multilayer Ceramic Capacitor MLCC X7R 1uF 25V 10%,Murata,GRM188R71E105KA12D,Mouser: 81-GRM188R71E105KA2D / LCSC: C15849
28,"C3, C5, C7, C9, C12, C16, C17, C18",8,100nF 50V,0603 (1608 Metric),Multilayer Ceramic Capacitor MLCC X7R 100nF 50V 10%,Yageo / Murata,CC0603KRX7R9BB104,Mouser: 603-CC603KRX7R9BB104 / LCSC: C14663
29,C11,1,10nF 50V,0603 (1608 Metric),Multilayer Ceramic Capacitor MLCC X7R 10nF 50V 10%,Yageo / Murata,CC0603KRX7R9BB103,Mouser: 603-CC603KRX7R9BB103 / LCSC: C57112
30,C19,1,4.7nF 50V,0603 (1608 Metric),Multilayer Ceramic Capacitor MLCC X7R 4.7nF 50V 10%,Yageo / Murata,CC0603KRX7R9BB472,Mouser: 603-CC603KRX7R9BB472 / LCSC: C57114
31,"R1, R19",2,100k 1%,0603 (1608 Metric),Thick Film Chip Resistor 100k Ohm 1/10W 1%,Yageo,RC0603FR-07100KL,Mouser: 603-RC0603FR-07100KL / LCSC: C25804
32,R2,1,24.9k 1%,0603 (1608 Metric),Precision Resistor 24.9k Ohm 1/10W 1% (LMR36510 Vout Feedback),Yageo,RC0603FR-0724K9L,Mouser: 603-RC0603FR-0724K9L / LCSC: C23171
33,"R3, R4, R15, R16, R22",5,1k 1%,0603 (1608 Metric),Thick Film Chip Resistor 1k Ohm 1/10W 1%,Yageo,RC0603FR-071KL,Mouser: 603-RC0603FR-071KL / LCSC: C21190
34,R5,1,47k 1%,0603 (1608 Metric),Thick Film Chip Resistor 47k Ohm 1/10W 1%,Yageo,RC0603FR-0747KL,Mouser: 603-RC0603FR-0747KL / LCSC: C25817
35,"R6, R7, R8, R9, R12, R13, R17",7,10k 1%,0603 (1608 Metric),Thick Film Chip Resistor 10k Ohm 1/10W 1%,Yageo,RC0603FR-0710KL,Mouser: 603-RC0603FR-0710KL / LCSC: C25804
36,"R10, R11, R20, R21",4,60.4 1%,0603 (1608 Metric),Precision Resistor 60.4 Ohm 1/10W 1% (Split CAN / Iso-SPI Termination),Yageo,RC0603FR-0760R4L,Mouser: 603-RC0603FR-0760R4L / LCSC: C23238
37,R18,1,100 1%,0603 (1608 Metric),Thick Film Chip Resistor 100 Ohm 1/10W 1%,Yageo,RC0603FR-07100RL,Mouser: 603-RC0603FR-07100RL / LCSC: C22775
